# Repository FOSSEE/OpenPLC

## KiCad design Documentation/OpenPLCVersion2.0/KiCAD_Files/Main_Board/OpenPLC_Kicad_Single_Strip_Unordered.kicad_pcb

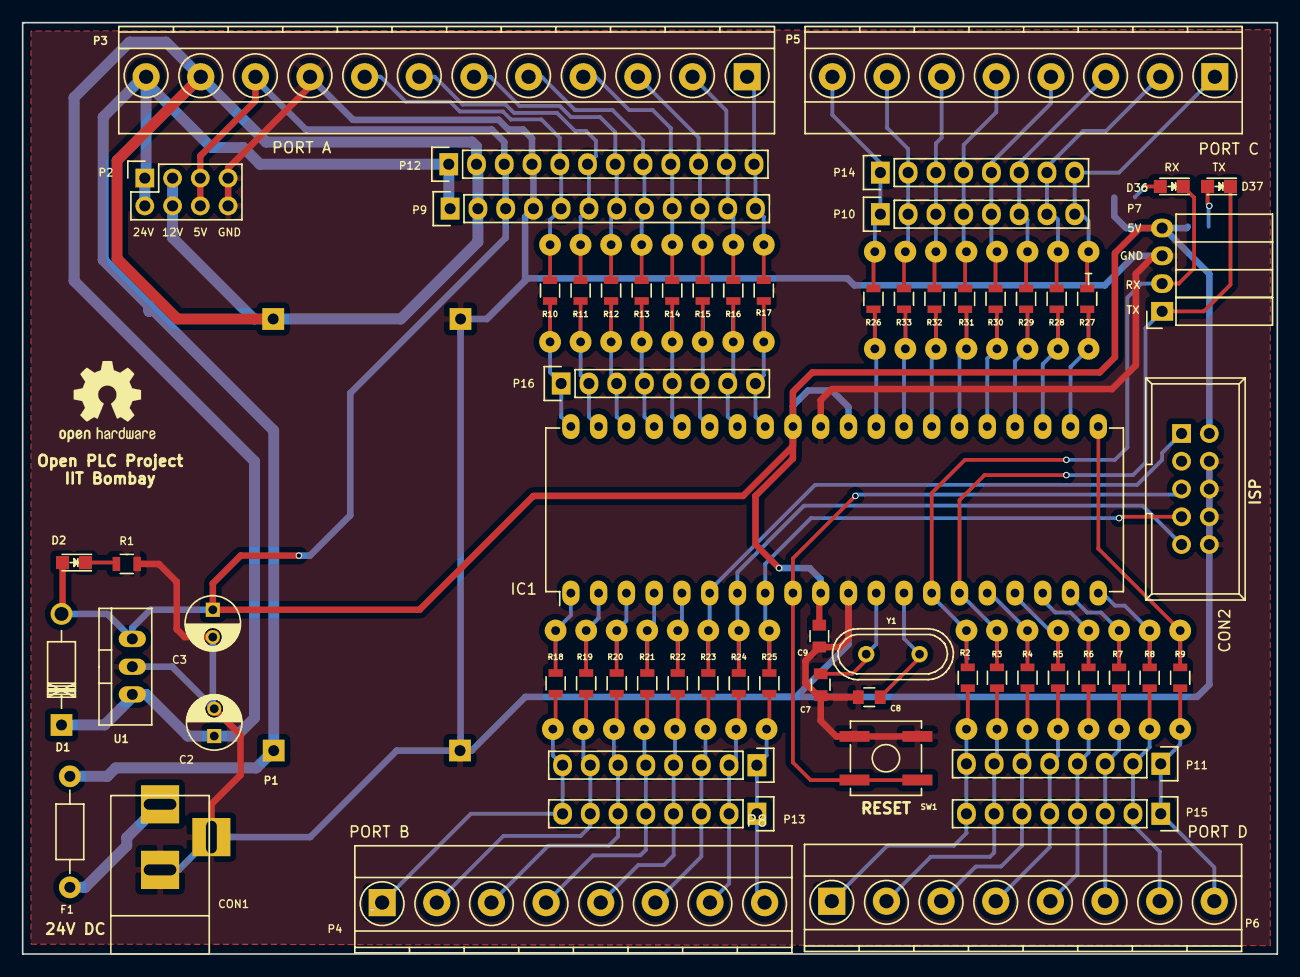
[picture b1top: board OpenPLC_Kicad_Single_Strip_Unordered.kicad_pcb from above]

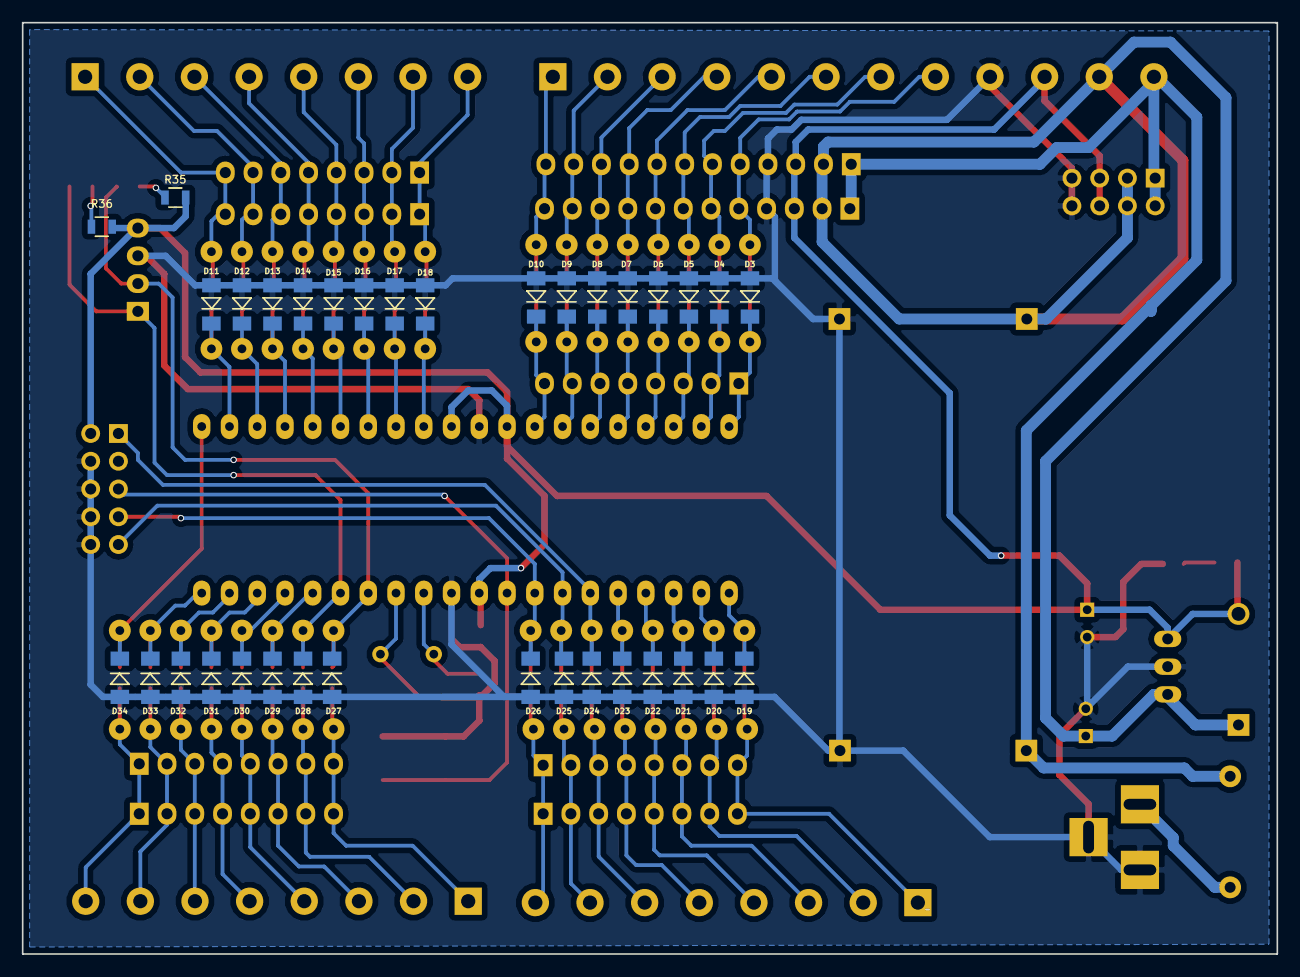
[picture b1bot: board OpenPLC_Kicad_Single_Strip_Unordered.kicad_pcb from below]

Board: 2 copper layers, 114.8 x 85.2 mm, 163 parts (34 on the bottom side), 75 nets.

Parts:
C2: 100uF; C_Radial_D5_L11_P2.5
C3: 10uF; C_Radial_D5_L11_P2.5
C7, C8: 22pF; C_0805
C9: 100nF; C_0805
CON1: BARREL_JACK
CON2: AVR-ISP-10; IDC_Header_Straight_10pins
D1: D; Diode_DO-41_SOD81_Horizontal_RM10
D2: LED; LED_0805
D3, D4, D5, D6, D7, D8, D9, D10, D11, D12, D13, D14, D15, D16, D17, D18, D19, D20, D21, D22, D23, D24, D25, D26, D27, D28, D29, D30, D31, D32, D33, D34: 5.1V; MiniMELF_Standard
D36: RX; LED_0805
D37: TX; LED_0805
F1: PTC; Resistor_Horizontal_RM10mm
IC1: ATMEGA16-P; DIP-40_W15.24mm_LongPads
P1: LM2596; LM2596s_New
P2: CONN_02X04; Socket_Strip_Straight_2x04
P3: PortA; TerminalBlock_Pheonix_MKDS1.5-12pol
P4: PortB; TerminalBlock_Pheonix_MKDS1.5-8pol
P5: PortC; TerminalBlock_Pheonix_MKDS1.5-8pol
P6: PortD; TerminalBlock_Pheonix_MKDS1.5-8pol
P7: Max232; Socket_Strip_Angled_1x04
P8: PortB_B; Socket_Strip_Straight_1x08
P9: PortA_B; Socket_Strip_Straight_1x12
P10: PortC_B; Socket_Strip_Straight_1x08
P11: PortD_B; Socket_Strip_Straight_1x08
P12: PortA_M; Pin_Header_Straight_1x12
P13: PortB_M; Pin_Header_Straight_1x08
P14: PortC_M; Pin_Header_Straight_1x08
P15: PortD_M; Pin_Header_Straight_1x08
P16: PortA_FM; Socket_Strip_Straight_1x08
R1: 470E; R_0805
R2, R3, R4, R5, R6, R7, R8, R9, R10, R11, R12, R13, R14, R15, R16, R17, R18, R19, R20, R21, R22, R23, R24, R25, R26, R27, R28, R29, R30, R31, R32, R33: 220E; R_0805
R35, R36: 1K; R_0805
SW1: SW_PUSH; SW_SPST_B3SL-1002P
U1: 7805; TO-220_Neutral123_Vertical
W1, W2, W3, W4, W5, W6, W7, W8, W9, W10, W11, W12, W13, W14, W15, W16, W17, W18, W19, W20, W21, W22, W23, W24, W25, W26, W27, W28, W29, W30, W31, W32, W33, W34, W35, W36, W37, W38, W39, W40, W41, W42, W43, W44, W45, W46, W47, W48, W49, W50, W51, W52, W53, W54, W55, W56, W57, W58, W59, W60, W61, W62, W63, W64: T; SolderWirePad_single_0-8mmDrill
Y1: 16Mhz; Crystal_HC49-U_Vertical

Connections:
5V: C3.1, C9.1, CON2.2, D1.2, D2.2, IC1.10, IC1.30, IC1.32, P2.5, P2.6, P3.10, P7.4, P9.3, P12.3, R35.2, R36.2, U1.3
12V: C2.1, D1.1, P1.2, P2.3, P2.4, P3.11, P9.2, P12.2, U1.1
24V: F1.2, P1.1, P2.1, P2.2, P3.12, P9.1, P12.1
/A0: D3.1, IC1.40, P16.1, R10.1, W1.1
/A1: D4.1, IC1.39, P16.2, R11.1, W2.1
/A2: D5.1, IC1.38, P16.3, R12.1, W5.1
/A3: D6.1, IC1.37, P16.4, R13.1, W9.1
/A4: D7.1, IC1.36, P16.5, R14.1, W13.1
/A5: D8.1, IC1.35, P16.6, R15.1, W17.1
/A6: D9.1, IC1.34, P16.7, R16.1, W21.1
/A7: D10.1, IC1.33, P16.8, R17.1, W25.1
/B0: D19.1, IC1.1, R18.1, W3.1
/B1: D20.1, IC1.2, R19.1, W6.1
/B2: D21.1, IC1.3, R20.1, W10.1
/B3: D22.1, IC1.4, R21.1, W14.1
/B4: D23.1, IC1.5, R22.1, W18.1
/C0: D11.1, IC1.22, R27.1, W4.1
/C1: D12.1, IC1.23, R28.1, W7.1
/C2: D13.1, IC1.24, R29.1, W11.1
/C3: D14.1, IC1.25, R30.1, W15.1
/C4: D15.1, IC1.26, R31.1, W19.1
/C5: D16.1, IC1.27, R32.1, W23.1
/C6: D17.1, IC1.28, R33.1, W27.1
/C7: D18.1, IC1.29, R26.1, W30.1
/D2: D29.1, IC1.16, R4.1, W16.1
/D3: D30.1, IC1.17, R5.1, W20.1
/D4: D31.1, IC1.18, R6.1, W24.1
/D5: D32.1, IC1.19, R7.1, W28.1
/D6: D33.1, IC1.20, R8.1, W31.1
/D7: D34.1, IC1.21, R9.1, W32.1
/MISO: CON2.9, D25.1, IC1.7, R24.1, W26.1
/MOSI: CON2.1, D24.1, IC1.6, R23.1, W22.1
/RST: CON2.5, IC1.9, SW1.2
/RX: D27.1, D36.1, IC1.14, P7.2, R2.1, W8.1
/SCK: CON2.7, D26.1, IC1.8, R25.1, W29.1
/TX: D28.1, D37.1, IC1.15, P7.1, R3.1, W12.1
GND: C2.2, C3.2, C7.1, C8.1, C9.2, CON1.2, CON1.3, CON2.4, CON2.6, CON2.8, CON2.10, D3.2, D4.2, D5.2, D6.2, D7.2, D8.2, D9.2, D10.2, D11.2, D12.2, D13.2, D14.2, D15.2, D16.2, D17.2, D18.2, D19.2, D20.2, D21.2, D22.2, D23.2, D24.2, D25.2, D26.2, D27.2, D28.2, D29.2, D30.2, D31.2, D32.2, D33.2, D34.2, IC1.11, IC1.31, P1.3, P1.4, P2.7, P2.8, P3.9, P7.3, P9.4, P12.4, R1.2, SW1.1, U1.2
unnamed: C7.2, IC1.12, Y1.1
unnamed: C8.2, IC1.13, Y1.2
unnamed: CON1.1, F1.1
unnamed: D2.1, R1.1
unnamed: D36.2, R35.1
unnamed: D37.2, R36.1
unnamed: P5.8, P10.1, P14.1, R26.2, W63.1
unnamed: P5.7, P10.2, P14.2, R33.2, W59.1
unnamed: P5.6, P10.3, P14.3, R32.2, W55.1
unnamed: P5.5, P10.4, P14.4, R31.2, W51.1
unnamed: P5.4, P10.5, P14.5, R30.2, W47.1
unnamed: P5.3, P10.6, P14.6, R29.2, W43.1
unnamed: P5.2, P10.7, P14.7, R28.2, W39.1
unnamed: P5.1, P10.8, P14.8, R27.2, W35.1
unnamed: P6.8, P11.1, P15.1, R9.2, W64.1
unnamed: P6.7, P11.2, P15.2, R8.2, W60.1
unnamed: P6.6, P11.3, P15.3, R7.2, W56.1
unnamed: P6.5, P11.4, P15.4, R6.2, W52.1
unnamed: P6.4, P11.5, P15.5, R5.2, W48.1
unnamed: P6.3, P11.6, P15.6, R4.2, W44.1
unnamed: P6.2, P11.7, P15.7, R3.2, W40.1
unnamed: P6.1, P11.8, P15.8, R2.2, W36.1
unnamed: P3.8, P9.5, P12.5, R10.2, W33.1
unnamed: P3.7, P9.6, P12.6, R11.2, W37.1
unnamed: P3.6, P9.7, P12.7, R12.2, W41.1
unnamed: P3.5, P9.8, P12.8, R13.2, W45.1
unnamed: P3.4, P9.9, P12.9, R14.2, W49.1
unnamed: P3.3, P9.10, P12.10, R15.2, W53.1
unnamed: P3.2, P9.11, P12.11, R16.2, W57.1
unnamed: P3.1, P9.12, P12.12, R17.2, W61.1
unnamed: P4.8, P8.1, P13.1, R25.2, W62.1
unnamed: P4.7, P8.2, P13.2, R24.2, W58.1
unnamed: P4.6, P8.3, P13.3, R23.2, W54.1
unnamed: P4.5, P8.4, P13.4, R22.2, W50.1
unnamed: P4.4, P8.5, P13.5, R21.2, W46.1
unnamed: P4.3, P8.6, P13.6, R20.2, W42.1
unnamed: P4.2, P8.7, P13.7, R19.2, W38.1
unnamed: P4.1, P8.8, P13.8, R18.2, W34.1

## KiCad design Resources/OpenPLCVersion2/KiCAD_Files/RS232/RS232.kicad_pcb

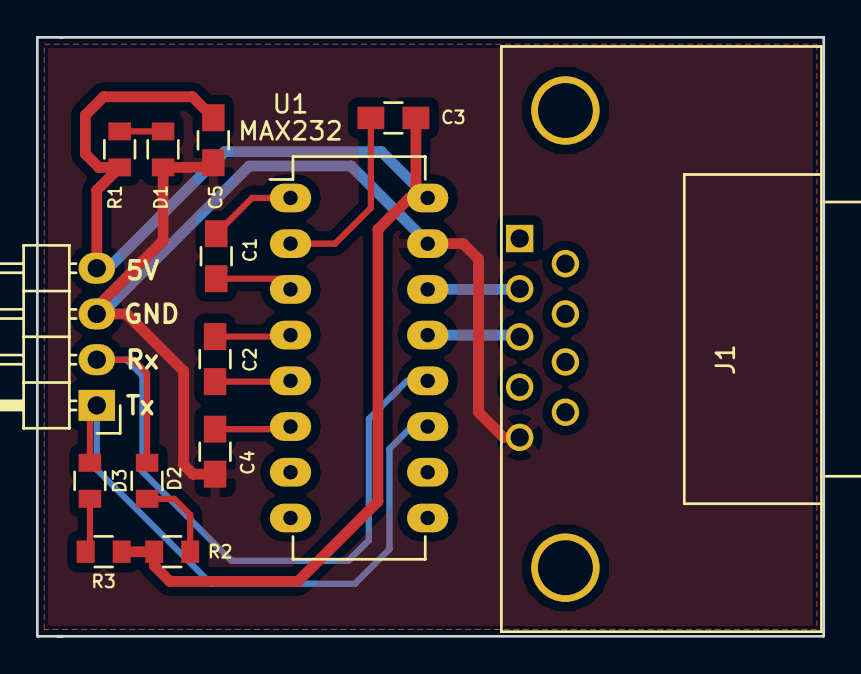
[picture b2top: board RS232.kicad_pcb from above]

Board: 2 copper layers, 43.7 x 33.3 mm, 14 parts (0 on the bottom side), 15 nets.

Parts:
C1, C2, C3, C4, C5: 1uF; C_0805_HandSoldering
D1, D2, D3: LED; C_0805
J1: DB9; DB9FC
P1: CONN_01X04; Pin_Header_Angled_1x04
R1, R2, R3: 1K; C_0805
U1: MAX232; DIP-16_W7.62mm_LongPads

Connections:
/5V: C3.2, C5.1, P1.4, R1.1, R2.1, R3.1, U1.16
/RX: D2.1, P1.2, U1.12
/TX: D3.1, P1.1, U1.11
GND: C4.1, C5.2, D1.1, J1.5, P1.3, U1.15
unnamed: C1.1, U1.1
unnamed: C1.2, U1.3
unnamed: C2.1, U1.4
unnamed: C2.2, U1.5
unnamed: C3.1, U1.2
unnamed: C4.2, U1.6
unnamed: D1.2, R1.2
unnamed: D2.2, R2.2
unnamed: D3.2, R3.2
unnamed: J1.2, U1.14
unnamed: J1.3, U1.13
